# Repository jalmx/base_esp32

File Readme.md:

# Base for ESP32 for DevKit V1

## Schematic

This board is a base to connect different components to test. Make easy life

## Silkscreen

## 3D

## Ray

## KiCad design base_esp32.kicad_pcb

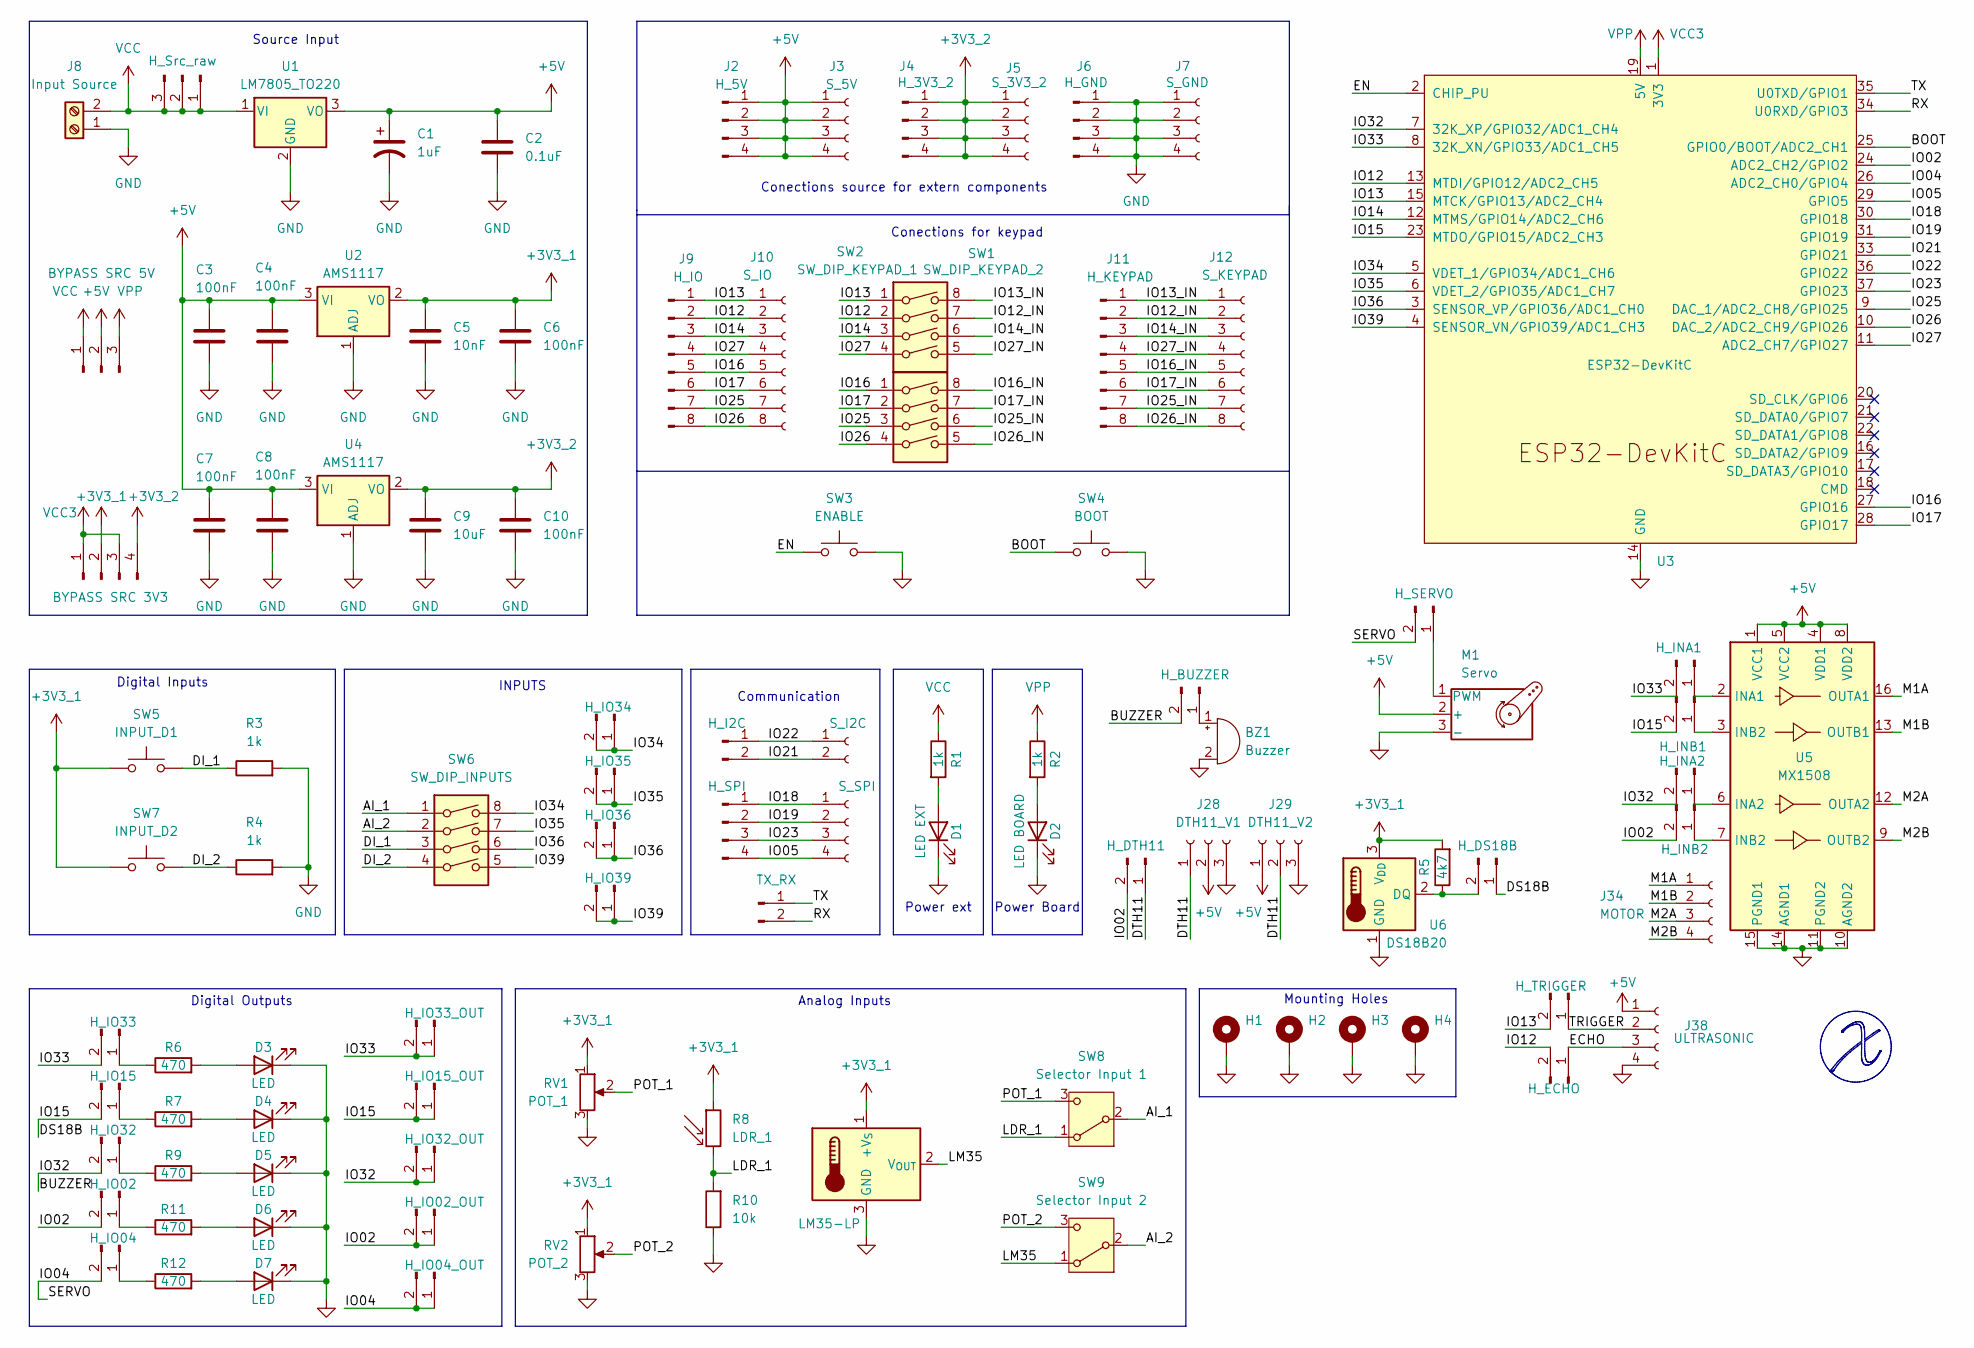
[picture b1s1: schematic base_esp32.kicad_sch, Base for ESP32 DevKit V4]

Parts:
BZ1: Buzzer; MagneticBuzzer_ProSignal_ABI-010-RC
C1: 1uF; CP_Radial_D5.0mm_P2.50mm
C2: 0.1uF; C_Disc_D5.0mm_W2.5mm_P5.00mm
C3, C4, C6, C7, C8, C10: 100nF; C_0805_2012Metric
C5: 10nF; C_0805_2012Metric
C9: 10uF; C_0805_2012Metric
D1: LED EXT; LED_0805_2012Metric
D2: LED BOARD; LED_0805_2012Metric
D3, D4, D5, D6, D7: LED; LED_D3.0mm
H1, H2, H3, H4: MountingHole_Pad; MountingHole_3mm_Pad_TopBottom
J1: H_Src_raw; PinHeader_1x03_P2.54mm_Vertical
J2: H_5V; PinHeader_1x04_P2.54mm_Vertical
J3: S_5V; PinSocket_1x04_P2.54mm_Vertical
J4: H_3V3_2; PinHeader_1x04_P2.54mm_Vertical
J5: S_3V3_2; PinSocket_1x04_P2.54mm_Vertical
J6: H_GND; PinHeader_1x04_P2.54mm_Vertical
J7: S_GND; PinSocket_1x04_P2.54mm_Vertical
J8: Input Source; TerminalBlock_Phoenix_PT-1,5-2-5.0-H_1x02_P5.00mm_Horizontal
J9: H_IO; PinHeader_1x08_P2.54mm_Vertical
J10: S_IO; PinSocket_1x08_P2.54mm_Vertical
J11: H_KEYPAD; PinHeader_1x08_P2.54mm_Vertical
J12: S_KEYPAD; PinSocket_1x08_P2.54mm_Vertical
J13: BYPASS SRC 5V; PinHeader_1x03_P2.54mm_Vertical
J14: BYPASS SRC 3V3; PinHeader_1x04_P2.54mm_Vertical
J15: H_SERVO; PinHeader_1x02_P2.54mm_Vertical
J16: H_INA1; PinHeader_1x02_P2.54mm_Vertical
J17: H_BUZZER; PinHeader_1x02_P2.54mm_Vertical
J18: H_INB1; PinHeader_1x02_P2.54mm_Vertical
J19: H_IO34; PinHeader_1x02_P2.54mm_Vertical
J20: H_I2C; PinHeader_1x02_P2.54mm_Vertical
J21: S_I2C; PinSocket_1x02_P2.54mm_Vertical
J22: H_IO35; PinHeader_1x02_P2.54mm_Vertical
J23: H_INA2; PinHeader_1x02_P2.54mm_Vertical
J24: H_INB2; PinHeader_1x02_P2.54mm_Vertical
J25: H_IO36; PinHeader_1x02_P2.54mm_Vertical
J26: H_SPI; PinHeader_1x04_P2.54mm_Vertical
J27: S_SPI; PinSocket_1x04_P2.54mm_Vertical
J28: DTH11_V1; PinSocket_1x03_P2.54mm_Vertical
J29: DTH11_V2; PinSocket_1x03_P2.54mm_Vertical
J30: H_DTH11; PinHeader_1x02_P2.54mm_Vertical
J31: H_DS18B; PinHeader_1x02_P2.54mm_Vertical
J32: H_IO39; PinHeader_1x02_P2.54mm_Vertical
J33: TX_RX; PinHeader_1x02_P2.54mm_Vertical
J34: MOTOR; PinSocket_1x04_P2.54mm_Vertical
J35: H_TRIGGER; PinHeader_1x02_P2.54mm_Vertical
J36: H_IO33_OUT; PinHeader_1x02_P2.54mm_Vertical
J37: H_IO33; PinHeader_1x02_P2.54mm_Vertical
J38: ULTRASONIC; PinSocket_1x04_P2.54mm_Vertical
J39: H_IO15; PinHeader_1x02_P2.54mm_Vertical
J40: H_IO15_OUT; PinHeader_1x02_P2.54mm_Vertical
J41: H_ECHO; PinHeader_1x02_P2.54mm_Vertical
J42: H_IO32; PinHeader_1x02_P2.54mm_Vertical
J43: H_IO32_OUT; PinHeader_1x02_P2.54mm_Vertical
J44: H_IO02; PinHeader_1x02_P2.54mm_Vertical
J45: H_IO02_OUT; PinHeader_1x02_P2.54mm_Vertical
J46: H_IO04; PinHeader_1x02_P2.54mm_Vertical
J47: H_IO04_OUT; PinHeader_1x02_P2.54mm_Vertical
M1: Servo; PinHeader_1x03_P2.54mm_Vertical
R1, R2: 1k; R_0805_2012Metric_Pad1.20x1.40mm_HandSolder
R3, R4: 1k; R_Axial_DIN0207_L6.3mm_D2.5mm_P10.16mm_Horizontal
R5: 4k7; R_Axial_DIN0207_L6.3mm_D2.5mm_P10.16mm_Horizontal
R6, R7, R9, R11, R12: 470; R_Axial_DIN0207_L6.3mm_D2.5mm_P10.16mm_Horizontal
R8: LDR_1; R_LDR_5.0x4.1mm_P3mm_Vertical
R10: 10k; R_Axial_DIN0207_L6.3mm_D2.5mm_P10.16mm_Horizontal
RV1: POT_1; Potentiometer_Alps_RK163_Single_Horizontal
RV2: POT_2; Potentiometer_Piher_PT-10-V05_Vertical
SW1: SW_DIP_KEYPAD_1; SW_DIP_SPSTx04_Slide_9.78x12.34mm_W7.62mm_P2.54mm
SW2: SW_DIP_KEYPAD_2; SW_DIP_SPSTx04_Slide_9.78x12.34mm_W7.62mm_P2.54mm
SW3: ENABLE; SW_PUSH_6mm
SW4: BOOT; SW_PUSH_6mm
SW5: INPUT_D1; SW_PUSH_6mm
SW6: SW_DIP_INPUTS; SW_DIP_SPSTx04_Slide_9.78x12.34mm_W7.62mm_P2.54mm
SW7: INPUT_D2; SW_PUSH_6mm
SW8: Selector Input 1; PinHeader_1x03_P2.54mm_Vertical
SW9: Selector Input 2; PinHeader_1x03_P2.54mm_Vertical
U1: LM7805_TO220; TO-220-3_Vertical
U2, U4: AMS1117; SOT-223-3_TabPin2; LCSC Part C22458961
U3: ESP32-DevKitC
U5: MX1508; SOP-16_3.9x9.9mm_P1.27mm
U6: DS18B20; TO-92_Inline
U7: LM35-LP; TO-92_Inline

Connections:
+3V3_1: C5.1, C6.1, J14.2, R5.2, R8.1, RV1.1, RV2.1, SW5.1, SW7.1, U2.2 (VO), U6.3 (V_{DD}), U7.1 (+V_{S})
+3V3_2: C9.1, C10.1, J4.1, J4.2, J4.3, J4.4, J5.1, J5.2, J5.3, J5.4, J14.4, U4.2 (VO)
+5V: C1.1, C2.1, C3.1, C4.1, C7.1, C8.1, J2.1, J2.2, J2.3, J2.4, J3.1, J3.2, J3.3, J3.4, J13.2, J28.2, J29.1, J38.1, M1.2 (+), U1.3 (VO), U2.3 (VI), U4.3 (VI), U5.1 (VCC1), U5.4 (VDD1), U5.5 (VCC2), U5.8 (VDD2)
/AI_1: SW6.1, SW8.2 (B)
/AI_2: SW6.2, SW9.2 (B)
/BOOT: SW4.1, U3.25 (GPIO0/BOOT/ADC2_CH1)
/BUZZER: J17.2, J23.2, J42.2, J43.1, J43.2, U3.7 (32K_XP/GPIO32/ADC1_CH4)
/DI_1: R3.1, SW5.2, SW6.3
/DI_2: R4.1, SW6.4, SW7.2
/DS18B: J18.2, J31.1, J39.2, J40.1, J40.2, U3.23 (MTDO/GPIO15/ADC2_CH3)
/DTH11: J28.1, J29.2, J30.1
/ECHO: J38.3, J41.1
/EN: SW3.1, U3.2 (CHIP_PU)
/IO02: J24.2, J30.2, J44.2, J45.1, J45.2, U3.24 (ADC2_CH2/GPIO2)
/IO04: J15.2, J46.2, J47.1, J47.2, U3.26 (ADC2_CH0/GPIO4)
/IO05: J26.4, J27.4, U3.29 (GPIO5)
/IO12: J9.2, J10.2, J41.2, SW1.2, U3.13 (MTDI/GPIO12/ADC2_CH5)
/IO12_IN: J11.2, J12.2, SW1.7
/IO13: J9.1, J10.1, J35.2, SW1.1, U3.15 (MTCK/GPIO13/ADC2_CH4)
/IO13_IN: J11.1, J12.1, SW1.8
/IO14: J9.3, J10.3, SW1.3, U3.12 (MTMS/GPIO14/ADC2_CH6)
/IO14_IN: J11.3, J12.3, SW1.6
/IO16: J9.5, J10.5, SW2.1, U3.27 (GPIO16)
/IO16_IN: J11.5, J12.5, SW2.8
/IO17: J9.6, J10.6, SW2.2, U3.28 (GPIO17)
/IO17_IN: J11.6, J12.6, SW2.7
/IO18: J26.1, J27.1, U3.30 (GPIO18)
/IO19: J26.2, J27.2, U3.31 (GPIO19)
/IO21: J20.2, J21.2, U3.33 (GPIO21)
/IO22: J20.1, J21.1, U3.36 (GPIO22)
/IO23: J26.3, J27.3, U3.37 (GPIO23)
/IO25: J9.7, J10.7, SW2.3, U3.9 (DAC_1/ADC2_CH8/GPIO25)
/IO25_IN: J11.7, J12.7, SW2.6
/IO26: J9.8, J10.8, SW2.4, U3.10 (DAC_2/ADC2_CH9/GPIO26)
/IO26_IN: J11.8, J12.8, SW2.5
/IO27: J9.4, J10.4, SW1.4, U3.11 (ADC2_CH7/GPIO27)
/IO27_IN: J11.4, J12.4, SW1.5
/IO33: J16.2, J36.1, J36.2, J37.2, U3.8 (32K_XN/GPIO33/ADC1_CH5)
/IO34: J19.1, J19.2, SW6.8, U3.5 (VDET_1/GPIO34/ADC1_CH6)
/IO35: J22.1, J22.2, SW6.7, U3.6 (VDET_2/GPIO35/ADC1_CH7)
/IO36: J25.1, J25.2, SW6.6, U3.3 (SENSOR_VP/GPIO36/ADC1_CH0)
/IO39: J32.1, J32.2, SW6.5, U3.4 (SENSOR_VN/GPIO39/ADC1_CH3)
/LDR_1: R8.2, R10.2, SW8.1 (A)
/LM35: SW9.1 (A), U7.2 (V_{OUT})
/M1A: J34.1, U5.16 (OUTA1)
/M1B: J34.2, U5.13 (OUTB1)
/M2A: J34.3, U5.12 (OUTA2)
/M2B: J34.4, U5.9 (OUTB2)
/POT_1: RV1.2, SW8.3 (C)
/POT_2: RV2.2, SW9.3 (C)
/RX: J33.2, U3.34 (U0RXD/GPIO3)
/TRIGGER: J35.1, J38.2
/TX: J33.1, U3.35 (U0TXD/GPIO1)
GND: BZ1.2 (-), C1.2, C2.2, C3.2, C4.2, C5.2, C6.2, C7.2, C8.2, C9.2, C10.2, D1.1 (K), D2.1 (K), D3.1 (K), D4.1 (K), D5.1 (K), D6.1 (K), D7.1 (K), H1.1, H2.1, H3.1, H4.1, J6.1, J6.2, J6.3, J6.4, J7.1, J7.2, J7.3, J7.4, J8.1, J28.3, J29.3, J38.4, M1.3 (-), R3.2, R4.2, R10.1, RV1.3, RV2.3, SW3.2, SW4.2, U1.2 (GND), U2.1 (ADJ), U3.14 (GND), U3.32 (GND), U3.38 (GND), U4.1 (ADJ), U5.10 (AGND2), U5.11 (PGND2), U5.14 (AGND1), U5.15 (PGND1), U6.1 (GND), U7.3 (GND)
unnamed: BZ1.1 (+), J17.1
unnamed: D1.2 (A), R1.2
unnamed: D2.2 (A), R2.2
unnamed: D3.2 (A), R6.2
unnamed: D4.2 (A), R7.2
unnamed: D5.2 (A), R9.2
unnamed: D6.2 (A), R11.2
unnamed: D7.2 (A), R12.2
unnamed: J15.1, M1.1 (PWM)
unnamed: J16.1, U5.2 (INA1)
unnamed: J18.1, U5.3 (INB2)
unnamed: J23.1, U5.6 (INA2)
unnamed: J24.1, U5.7 (INB2)
unnamed: J31.2, R5.1, U6.2 (DQ)
unnamed: J37.1, R6.1
unnamed: J39.1, R7.1
unnamed: J42.1, R9.1
unnamed: J44.1, R11.1
unnamed: J46.1, R12.1
VCC: J1.1, J1.2, J1.3, J8.2, J13.1, R1.1, U1.1 (VI)
VCC3: J14.1, J14.3, U3.1 (3V3)
VPP: J13.3, R2.1, U3.19 (5V)

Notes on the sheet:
Conections for keypad
Conections source for extern components
Source Input
Digital Inputs
INPUTS
Digital Outputs
Power ext
Power Board
Analog Inputs
Mounting Holes
Communication

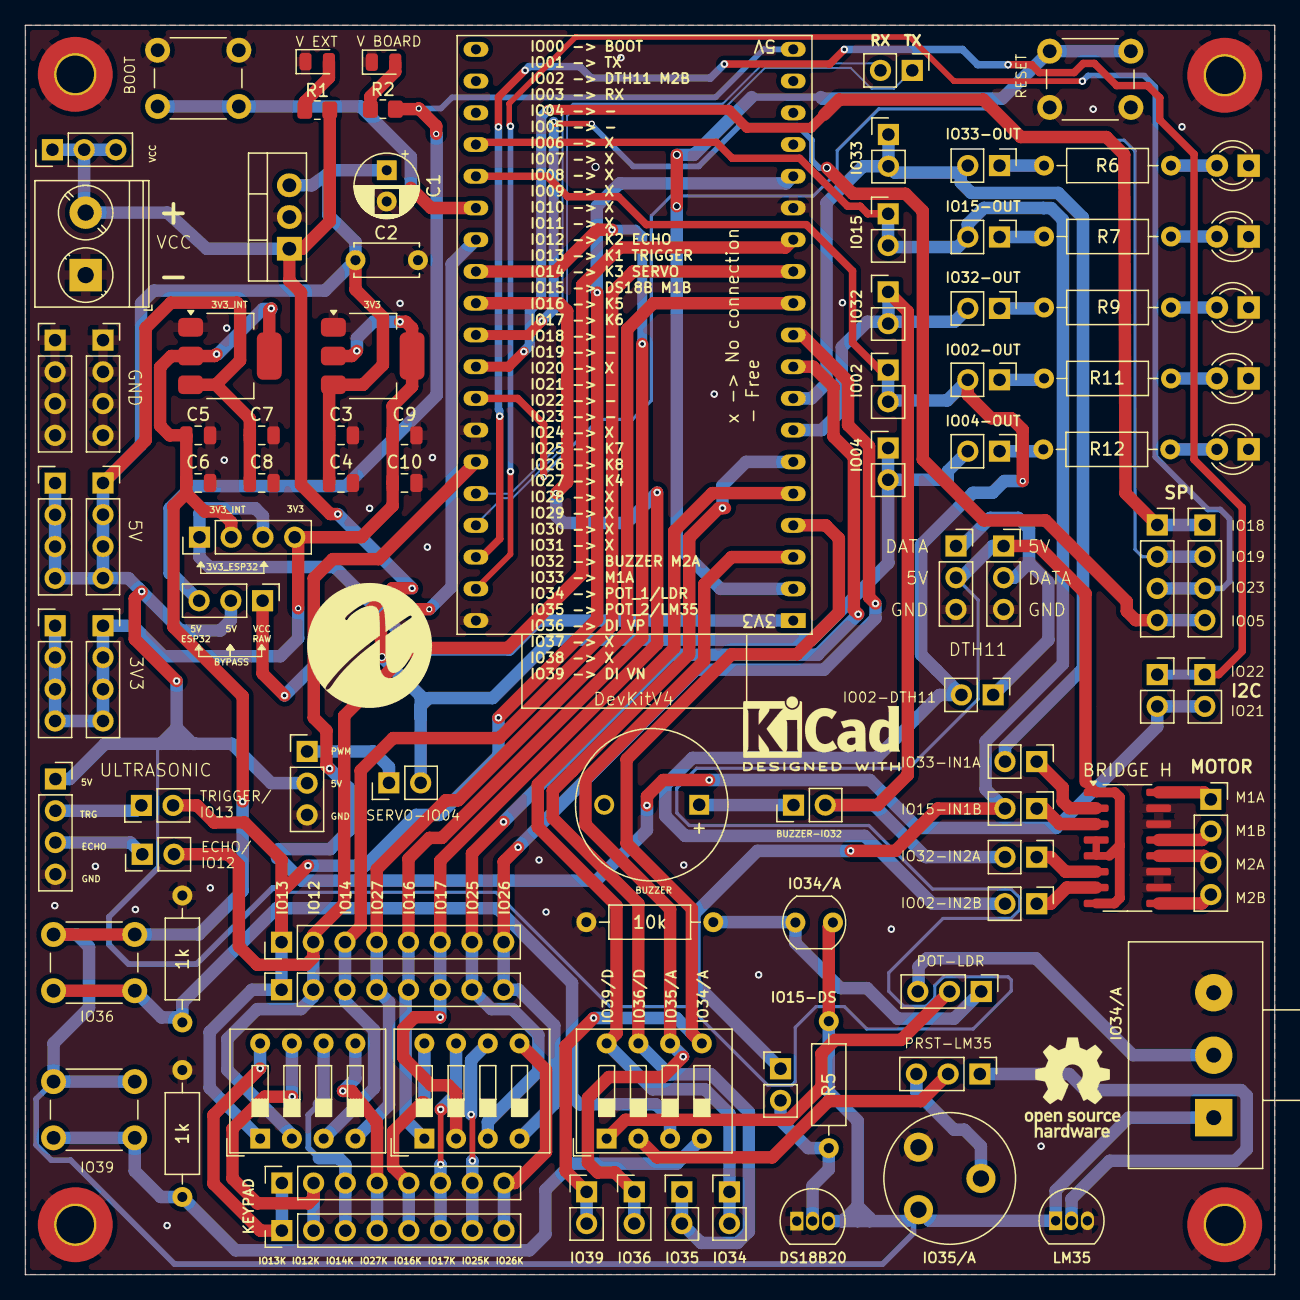
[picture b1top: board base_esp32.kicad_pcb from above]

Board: 2 copper layers, 100.0 x 100.0 mm, 100 parts (0 on the bottom side), 76 nets.

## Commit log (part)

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2024-11-27 init
2024-11-28 add: schematic
2024-11-28 mod: gitignore
2024-11-28 add: bypass source
2024-11-28 fix: vpp for board
2024-11-28 fix: ERC
2024-11-28 add: footprints, not done yet
2024-11-30 fix: schematic & footprint done
2024-11-30 update: schematic pdf
2024-11-30 add: led to power board
2024-11-30 add: mounting holes
2024-11-30 fix: package to sw5 dip
2024-12-01 fix: footprints
2024-12-01 fix: pot2 and change footprint
2024-12-01 fix: some tags for pcb, sorting elements
2024-12-08 add: some components to schematic
2024-12-15 rm: header
2024-12-15 add: ultrasonic
2024-12-19 add: router
2024-12-30 add: mark
2024-12-31 add: svg to fritzing in progress
2025-01-03 add: esp32 devkit v1
2025-01-04 add: esp32 devkit v1 schematic
2025-01-04 add: finish v0.1 devkit v4
2025-01-04 change: devkit v1
2025-01-05 release: v0.0.1 v1
2025-01-05 add: step v1
2025-01-05 fix: f silkscreen
